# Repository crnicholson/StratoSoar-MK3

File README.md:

# StratoSoar MK3 - UAVs For the Masses

<!-- **TL;DR**: The StratoSoar project is a low-cost, lightweight UAV designed to be dropped from a weather balloon  at any altitude, aiming for autonomous, efficient flight to selected GPS coordinates. The hope is to get a UAV platform in the hands of educators, researchers, and hobbyists alike since StratoSoar is much smaller, lighter, and cheaper than conventional UAVs.  -->

**TL:DR**: The StratoSoar project is a low-cost, lightweight Unmanned Aerial Vehicle (UAV) designed for deployment from a weather balloon at various altitudes, aiming for autonomous and efficient flight to designated GPS coordinates. By offering a more affordable, compact, and lightweight alternative to conventional UAVs, StratoSoar aims to empower educators, researchers, and hobbyists with an accessible platform for exploration and experimentation. 

## Watch The Video

<!-- **WORK IN PROGRESS** - This project is still in the works. I don't recommend using it yet because it has the potential of being dangerous.

**NEW** - Writing code and making the PCB. 

**STATE as of 7/1/24** - Just starting development! -->

<!-- <div style="max-width: 500px; margin: 0 auto;">
  <div style="position: relative; padding-bottom: 56.25%; height: 0; overflow: hidden; max-width: 100%; height: auto;">
    <iframe style="position: absolute; top: 0; left: 0; width: 100%; height: 100%;" src="https://www.youtube.com/embed/TiqkcGWG4g8" title="StratoSoar MK2/3: A Review" frameborder="0" allow="accelerometer; autoplay; clipboard-write; encrypted-media; gyroscope; picture-in-picture; web-share" referrerpolicy="strict-origin-when-cross-origin" allowfullscreen></iframe>
  </div>
</div>

<br /> -->

 | 
-- | --
<i>StratoSoar glider.</i> | <i>StratoSoar MK3.0 circuit board.</i>
 | 
<i>Computational fluid dynamic sims.</i> | <i>Soldering of the board.</i>

## What Is the StratoSoar Project?

StratoSoar is a low-power, adaptive UAV that is dropped from a weather balloon at approximately 5,000 feet, with plans to reach even higher altitudes soon. The main goal of StratoSoar is to fly to selected GPS coordinates efficiently or choose a closer, more realistic landing site without human interaction. The current aim for StratoSoar is to operate on a single 600 mAh 15 gram LiPo battery for a 10+ hour flight. 

## Now, What Is a UAV?

UAVs, or Unmanned Aerial Vehicles, are autonomous aircraft, usually in the form of planes or drones. They have many applications, such as [delivering medicine, food, and supplies](https://www.flyzipline.com/) to remote areas, participating in aerial combat with the military, and conducting aerial imaging.

### Common Types of UAVs Include:

- Quadcopter (typical drones)
- Fixed-wing aircraft (like StratoSoar)

## StratoSoar vs. Conventional UAVs

### Traditional UAVs Are Typically:

- Large (5-15 meter wingspan)
- Heavy (2-20 kg)
- Expensive ($10,000-10,000,000 USD)
- Closed source and proprietary

### StratoSoar Aims to Overcome These Limitations With:

- Weight: less than 250 grams
- Wingspan: 80 cm
- Cost: less than $150 USD
- Open source and accessible

## What Are the Uses of StratoSoar?

I'm currently considering two main concepts: an educational kit for students and hobbyists or a platform designed to study the aerodynamics of the stratosphere, a field with limited existing resources. Additionally, I'm exploring other ideas such as reusable radiosondes, systems for remote delivery of medicine and parcels, and advanced atmospheric monitoring solutions.

<!-- ## What Includes the StratoSoar Project? What Are the Different Parts of it?

StratoSoar has many different parts, and they all combine to make this project. 

- **Code** - All of the code directory, and the programs needed to run it. These include the main `.ino`s and the accompanying `.cpp` and `.h` files, along with the test files for the IMU and GPS.
- **PCB** - The circuit board is the basis of this project, it interfaces the code with the glider. StratoSoar includes the circuit board files and the schematics and everything needed to build a PCB.
- **3D Files** - StratoSoar requires some 3D printed parts to function, but these files also serve as an interactive build guide. StratoSoar includes the 3D files needed to print parts for the glider and the 3D files to assemble the glider.
- **Media** - The images and such of StratoSoar. 
- **Cutdown Mechanism** - This is the thing that helps you release the glider from the balloon payload - or whatever you want to drop it from. This includes all of the above things but will be in a separate GitHub repository.  -->

## How Does StratoSoar Work at a High Level?

<!-- StratoSoar is attached to a weather balloon via the cutdown mechanism. Once the balloon reaches the desired altitude, the cutdown mechanism drops the glider. The glider then descends, steering its way to specified coordinates. 

StratoSoar takes pride in being highly configurable and hackable, so there are many ways you change how it comes down built into the code. 

StratoSoar uses data from an IMU that goes through a Kalman filter to receive accurate AHRS, or Attitude Heading Reference System. This can tell StratoSoar the pitch, yaw, and roll of the glider. Then, StratoSoar integrates a GPS module to get the GPS coordinates. Both the GPS and the AHRS are used to compute the azimuth to find the turning angle of the glider. The turning angle tells the glider how much it needs to turn to be facing the correct yaw that will get the glider to the target location. Additionally, an algorithm is used to get the distance between the glider location's and the target location. 

With the turning angle computed, a PID mechanism is used to control the servo attached to the rudder of the glider. This PID mechanism learn from it's mistakes and can accurately aim the glider in the correct direction. 

Additionally, the glider beacons it's location at a configurable interval with LoRa for tracking. It also allows for a camera module to be added on to take photos and video. 

The glider will fly to the selected coordinates, and depending on the user configuration, will either spiral down or release a parachute above the coordinates once it has reached them to safely descend. Additionally, if the glider is too low in altitude, prior to the flight the user can enter closer coordinates as backup landing locations.  -->

StratoSoar MK3 is an advanced autonomous glider designed to operate at high altitudes, such as those reached by weather balloons. The glider is attached to a weather balloon via a cutdown mechanism. Once the balloon reaches the desired altitude, the cutdown mechanism releases the glider, initiating its descent. The glider then navigates autonomously to specified coordinates, using a combination of sensors, advanced algorithms, and low-power electronics.

### Core Components and Functionality:

- **Autopilot System**:
    - **GPS and IMU Integration**: StratoSoar uses a custom GPS module and an IMU, both designed for low-power operation. The IMU data is processed through a Kalman filter to provide accurate Attitude Heading Reference System (AHRS) data, including pitch, yaw, and roll. This information, combined with GPS coordinates, enables precise navigation.
    - **Advanced Waypoint Navigation**: The waypoint navigation system is designed for complex flight paths, incorporating advanced turning algorithms to ensure smooth and accurate direction changes.
    - **Servo Control with PID**: A PID control mechanism governs the rudder’s servo, ensuring precise adjustments to the glider's course based on real-time feedback.

- **Communication and Data Logging**:
    - **LoRa Telemetry**: The glider continuously beacons its location via LoRa communication, which includes forward error correction for reliable data transmission. This allows for real-time tracking and data collection.
    - **Data Logging**: Critical flight data, including sensor readings and GPS coordinates, are logged using a combination of SD card and EEPROM storage, optimized for low power consumption.
    - **Camera**: If configured, the glider uses a custom designed camera module to take photos at specific coordinates or record the entire flight.  

- **Modularity and Customization**:
    - **Hackability**: StratoSoar is designed to be highly configurable and hackable. Users can customize its descent strategy, whether by spiral descent, parachute deployment, or alternative landing locations. The codebase is modular, allowing for easy modifications or the addition of new features.
    - **Camera Module**: An optional low-power camera module can be added to capture photos or video during the flight, with Python scripts available for post-processing the footage.

- **Ground Station and Data Handling**:
    - **Ground Station**: The ground station, built on an ESP32 platform, receives telemetry data from the glider via LoRa. It logs this data locally and communicates with a server using HTTP requests. A Flask-based uploader script then transfers the data to SondeHub for analysis and storage.

- **PCB Design**:
    - **StratoSoar MK3 PCB**: The main PCB, optimized for power efficiency, size, and cost, integrates over 100 components, managing the various systems onboard.
    - **Additional PCBs**: Supporting PCBs, such as those for the GPS module, LoRa communication, camera, and IMU, are designed for specific tasks, enhancing the glider's overall functionality.

### Operation and Recovery:

Upon release from the weather balloon, StratoSoar begins its guided descent following waypoints or single target coordinate. It calculates the optimal flight path using its GPS and AHRS data, making real-time adjustments to its trajectory through the PID-controlled servo system. Depending on user configurations, the glider can either glide smoothly to the target coordinates, initiate a spiral descent, or deploy a parachute for a safe landing.

If the glider's altitude drops below a certain threshold, backup landing coordinates can be used to ensure a safe recovery. Throughout the flight, the glider’s location is continuously transmitted, allowing for easy tracking and recovery.

## File System and More Project Info

I'm only listing the key items, leaving out all the unnecessary stuff. This should give you a general sense of the project and all its features. Note that this is also only stuff I did during Hack Club Arcade.

- `Code/autopilot`: (5000 lines of code!)
    - `autopilot.ino`: The script that ties all of these files together.
    - `gps.cpp`: GPS code custom-made for low-power.
    - `waypoint.cpp`: Custom waypoint flight with advanced turning.
    - `lora.cpp`: LoRa communications with complex forward error correction.
    - `sd.cpp` + `eeprom.cpp`: Data logging in a low-power manner.
    - `servo.cpp`: Ultra low-power servo functions.
    - `bme280.cpp`: Weather data sensor.
    - `imu.cpp`: An interial measurement unit running a Kalman filter.
- `Code/groundStation`: 
    - `groundStation.ino`: The code for the receiving station of the LoRa telemetry, uses ESP32 and HTTP requests to communicate with the server, also locally logs data. 
    - `uploader/flaskUploader.py`: A Flask server that uses an API to put all the data on SondeHub. 
- `Code/camera`: Utilization of a low-power camera module and Python scripts for conversion.
- `Code/calculator`: Python script to parametrically create flying wing glider. 
- `PCB/StratoSoar-MK3.0`: The main PCB consisting of over 100 components, optimized for power, size, and cost.
- `PCB/gpsBreakout`: A PCB designed for testing a cheap, $2 Chinese GPS module.
- `PCB/loRa`: The ground station to receive the glider's data. 
- `PCB/camera`: A breakout board for a low-power camera module. 
- `PCB/imuBreakout`: One of the first breakout boards made for a new Interial Measurement Unit. 
- `3D Files/cardboardGlider`: Parametric Fusion 360 design for a folding origami glider. 
- `3D Files/StratoSoar Rev2 v36`: High efficiency glider.

## A Quick Note on MK1, MK2, Naming, and Revisions

StratoSoar MK1 was the precursor and the spark to StratoSoar MK2. StratoSoar MK1 was officially developed from October 1st to July 30th, although StratoSoar MK2 was unofficially being worked on in the months of March through June. StratoSoar MK1 failed to fly autonomously, and it also failed to release from the balloon. Major upgrades have been made since then.

StratoSoar MK2 officially started on October 1st, and will end has now ended. It was a success. 

StratoSoar MK3 officially started on June 1st, and will end in quite some time when I launch it from a weather balloon. A new major revision (eg. MK4) will come out every time when I release the glider from the balloon in the Summer. After the Summer, work on the next revision begins, with many updates and new features. 

<!-- A new sub-revision (for lack of better word) comes out every time I make a new PCB. For example, my first version of my PCB was MK2.0. At the time of writing, the current version of StratoSoar is MK2.1. A new version of 3D model is denoted by the Rev number. Rev starts at 0. 0 and 1 are not shown in this repo because they didn't turn out very good. The physical gliders are denoted by the 3D model number. Sometimes a small change is made with glider so the name of the glider is Rev x.x, for example. Sometimes the same happens with the 3D model, again it would be x.x. To put this in practice, the final glider may be MK2.5 Rev 7.3.1. The code has no version history in the way the 3D models and the PCB do. -->

Also, I use "we" a lot in this writing. This usually refers to myself or this project, but it also refers to my small team over at New England Weather Balloon Society.

One last thing. When I refer to StratoSoar, I am referring to the project as a whole, but more specifically, the most recent version. 

<!-- ## Watch my Talk About StratoSoar MK2 The North East HamXpo! -->

## Is This Legal?
Yes! During flight, the ground operator has no ***direct*** control over the flight path, i.e. via a radio. Because of this, and it being unpowered, it qualifies as a free flight glider. Free flight gliders have very little regulations. You can think of them as a paper airplane. 

## Can I Buy a Kit or a Complete Product?

Currently, StratoSoar is not available to purchase online as a kit or complete product. We have plans in the next few years to release a kit for schools, education centers, hobbyists and a complete product for industry at an affordable price. You are welcome to make one in the mean time!

## How Can I Make One? Are There Docs?

One of the goals of StratoSoar was to make an affordable and open source system for anyone to perform stratospheric research, so all the files are available for free. This means that you can construct StratoSoar from scratch. **A guide to do this will be available soon.**

<!-- It is still in the works, but you can check out `DOCS.md` under the `Docs` folder.**  -->

## Helpful Sources and Credits

I'm in the midst of compiling this.

## Cutdown Mechanism

[See my other WIP GitHub repo.](https://github.com/crnicholson/Cutdown-Mechanism)

## Funding and Support

We currently have <u>**very**</u> limited funding to complete this project. We would **love any donations or sponsorships** we could get to elevate (no pun intended) this project to the next level. If you don't want to donate, but want to help out, we would love your support with other areas of this project. Reach out to me if you have interest at:

- [newbsballoons@gmail.com](mailto:newbsballoons@gmail.com) (organization email, recommended).

- [charlienicholsonr@gmail.com](mailto:charlienicholsonr@gmail.com) (personal email).

## Special Thanks

This project would not be possible without the following individuals:

- Max Kendall (W0MXX) for working closely together with me.

- Mike Malis for helping with the design of the glider. 

- Brett Miwa for schematic review, PCB design, electrical theory, and boost converter circuitry design.

- Bob Phinney (K5TEC) for providing NEST and securing funding.

- Mark Jessop (VK5QI) for answering all of my questions.

- Mike Hojnowski (KD2EAT) for PCB design and hardware/software debugging.

- Paul Hamilton for helping me with FAA regulations.

- My parents!

And these entities:

- Hack Club, for providing support for projects like this. 

- New England Sci-Tech (NEST) for providing a maker space to work, funding, and hosting NEWBS.

- New England Weather Balloon Society (NEWBS) for expertise and the opportunity.

- Bagel Fund, for providing funding. 

## Affiliate Programs and Projects

- **Hack Club** - Hack Club is a non-profit designed for teenagers that provides support for projects like this. 
- **NEWBS** - Max and Seth Kendall of NEWBS, or New England Weather Balloon Society, are helping me launch my project from a balloon. They are dedicated to helping people in New England launch weather balloons. 
- **New England Sci-Tech** - Bob Phinney of NEST is hosting NEWBS. NEST is a great maker space. If you are in the Greater Boston Area, go check them out!
- **StratoScience** - This is the official class that I'm in helping me launch my project. This is a high altitude engineering class for teens. Check them out if your are in the Greater Boston area!

## Still Have Questions?

Do you have any questions? Are the docs incomplete and you want to ask anything? Do you just want to say hi (or how cool my project is!)?

Reach out to me at [charlienicholsonr@gmail.com](mailto:charlienicholsonr@gmail.com).

## Flights

# Mid August

The glider was realeased from 5,000 feet. You can see the launch video [here](https://www.youtube.com/watch?v=DZU_8TDUlJg). You can find data on the release [here](https://www.youtube.com/watch?v=TiqkcGWG4g8).

## License

Both the software and documentation are under the [GNU GPL v3 license](https://choosealicense.com/licenses/gpl-3.0/). The hardware and the 3D files are under the [CERN Open Hardware Licence Version 2 - Strongly Reciprocal](https://choosealicense.com/licenses/cern-ohl-s-2.0/). The media is under the [CC BY 4.0 DEED](https://creativecommons.org/licenses/by/4.0/).

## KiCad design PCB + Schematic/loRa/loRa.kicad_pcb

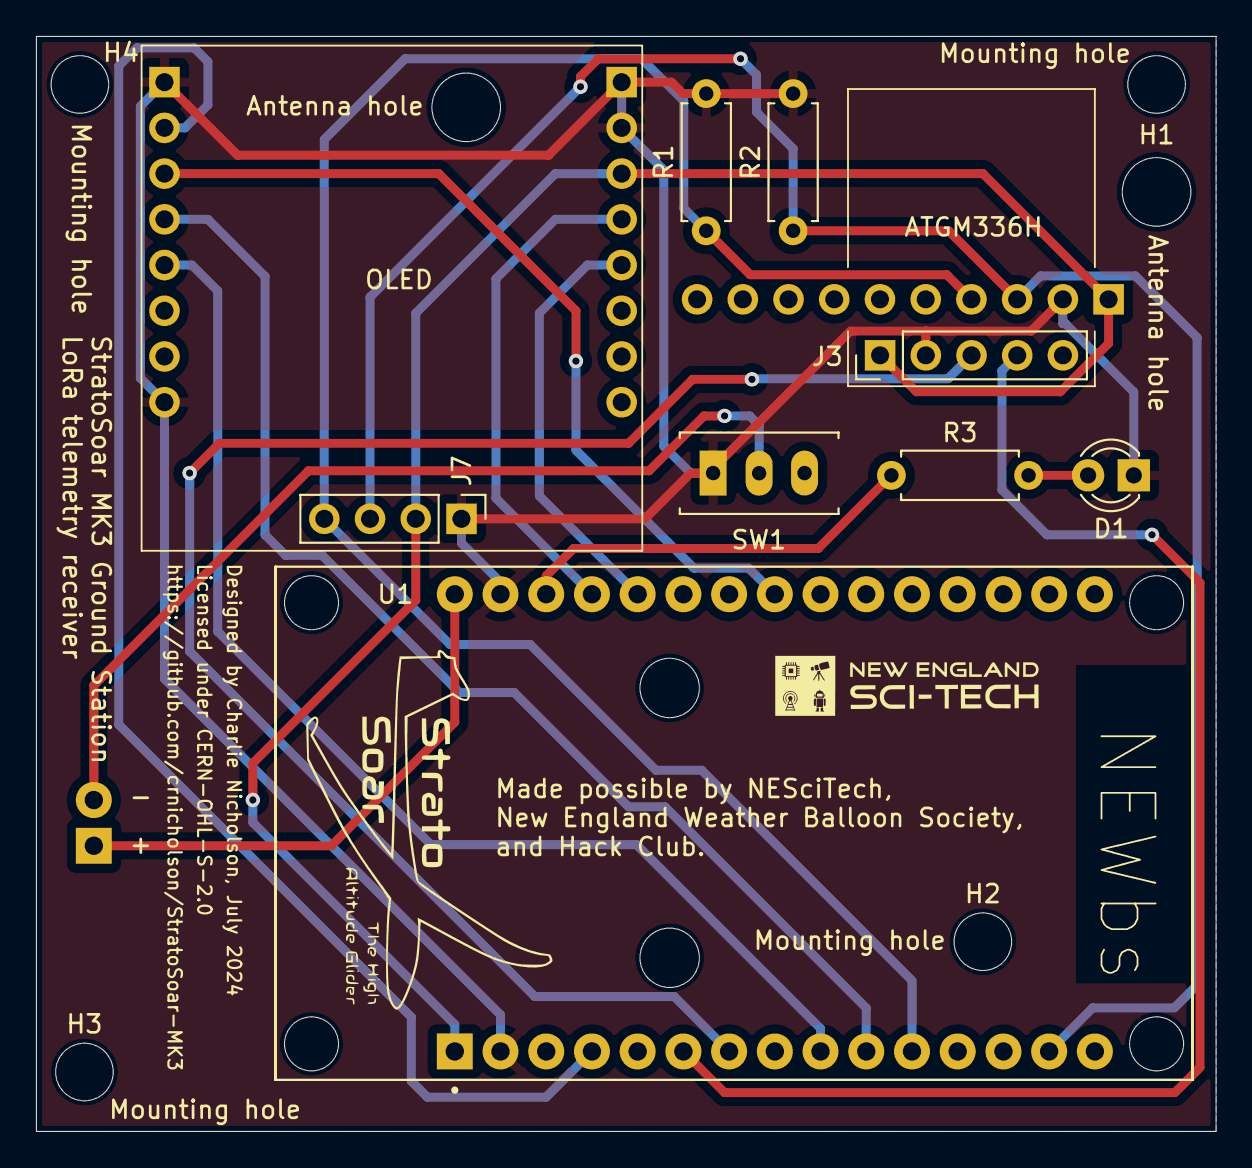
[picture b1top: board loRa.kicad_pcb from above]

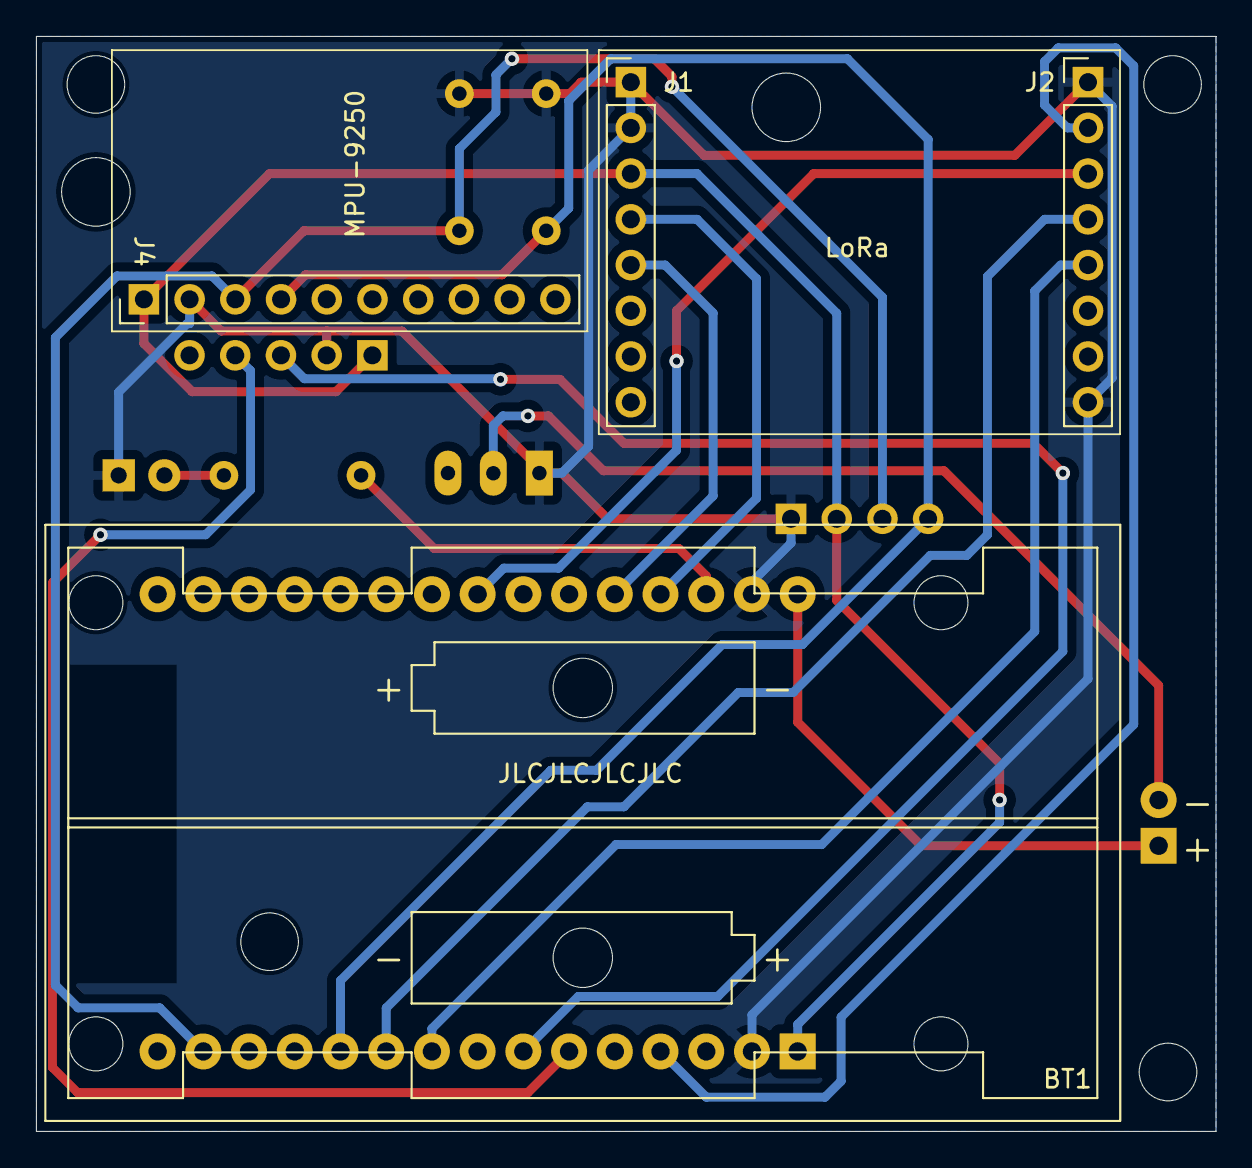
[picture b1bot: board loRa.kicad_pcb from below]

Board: 2 copper layers, 65.5 x 60.8 mm, 16 parts (4 on the bottom side), 16 nets.

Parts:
BT1: 3V; BatteryHolder_Keystone_2462_2xAA
D1: RED; LED_D3.0mm
H1, H2, H3, H4: MountingHole; MountingHole_3.2mm_M3
J1: Left; PinHeader_1x08_P2.54mm_Vertical
J2: Right; PinHeader_1x08_P2.54mm_Vertical
J3: GPS; PinHeader_1x05_P2.54mm_Vertical
J4: MPU-9250; PinHeader_1x10_P2.54mm_Vertical
J7: OLED; PinHeader_1x04_P2.54mm_Vertical
R1, R2: 1.8 K; R_Axial_DIN0207_L6.3mm_D2.5mm_P7.62mm_Horizontal
R3: 1 K; R_Axial_DIN0207_L6.3mm_D2.5mm_P7.62mm_Horizontal
SW1: SW_SPDT; SW_Slide_SPDT
U1: ESP32-DEVKIT-V1; MODULE_ESP32_DEVKIT_V1

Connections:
+3.3V: J1.3, J3.1, J4.1, J7.2, U1.1 (3V3)
+BATT: BT1.1 (+), U1.30 (VIN)
CS: J2.2, U1.4 (D2)
DIO0: J1.5, U1.26 (D14)
GND: D1.1 (K), J1.1, J1.2, J2.1, J2.8, J3.2, J4.2, J7.1, R1.2, R2.2, SW1.1 (A), U1.2 (GND), U1.29 (GND)
LED: R3.1, U1.28 (D13)
LORA_RST: J1.4, U1.27 (D12)
MISO: J2.4, U1.10 (D19)
MOSI: J2.3, U1.23 (D25)
unnamed: BT1.2 (-), SW1.2 (B)
unnamed: D1.2 (A), R3.2
RX: J3.4, U1.6 (RX2)
SCK: J2.5, U1.9 (D18)
SCL: J4.3, J7.3, R2.1, U1.14 (D22)
SDA: J4.4, J7.4, R1.1, U1.11 (D21)
TX: J3.3, U1.7 (TX2)

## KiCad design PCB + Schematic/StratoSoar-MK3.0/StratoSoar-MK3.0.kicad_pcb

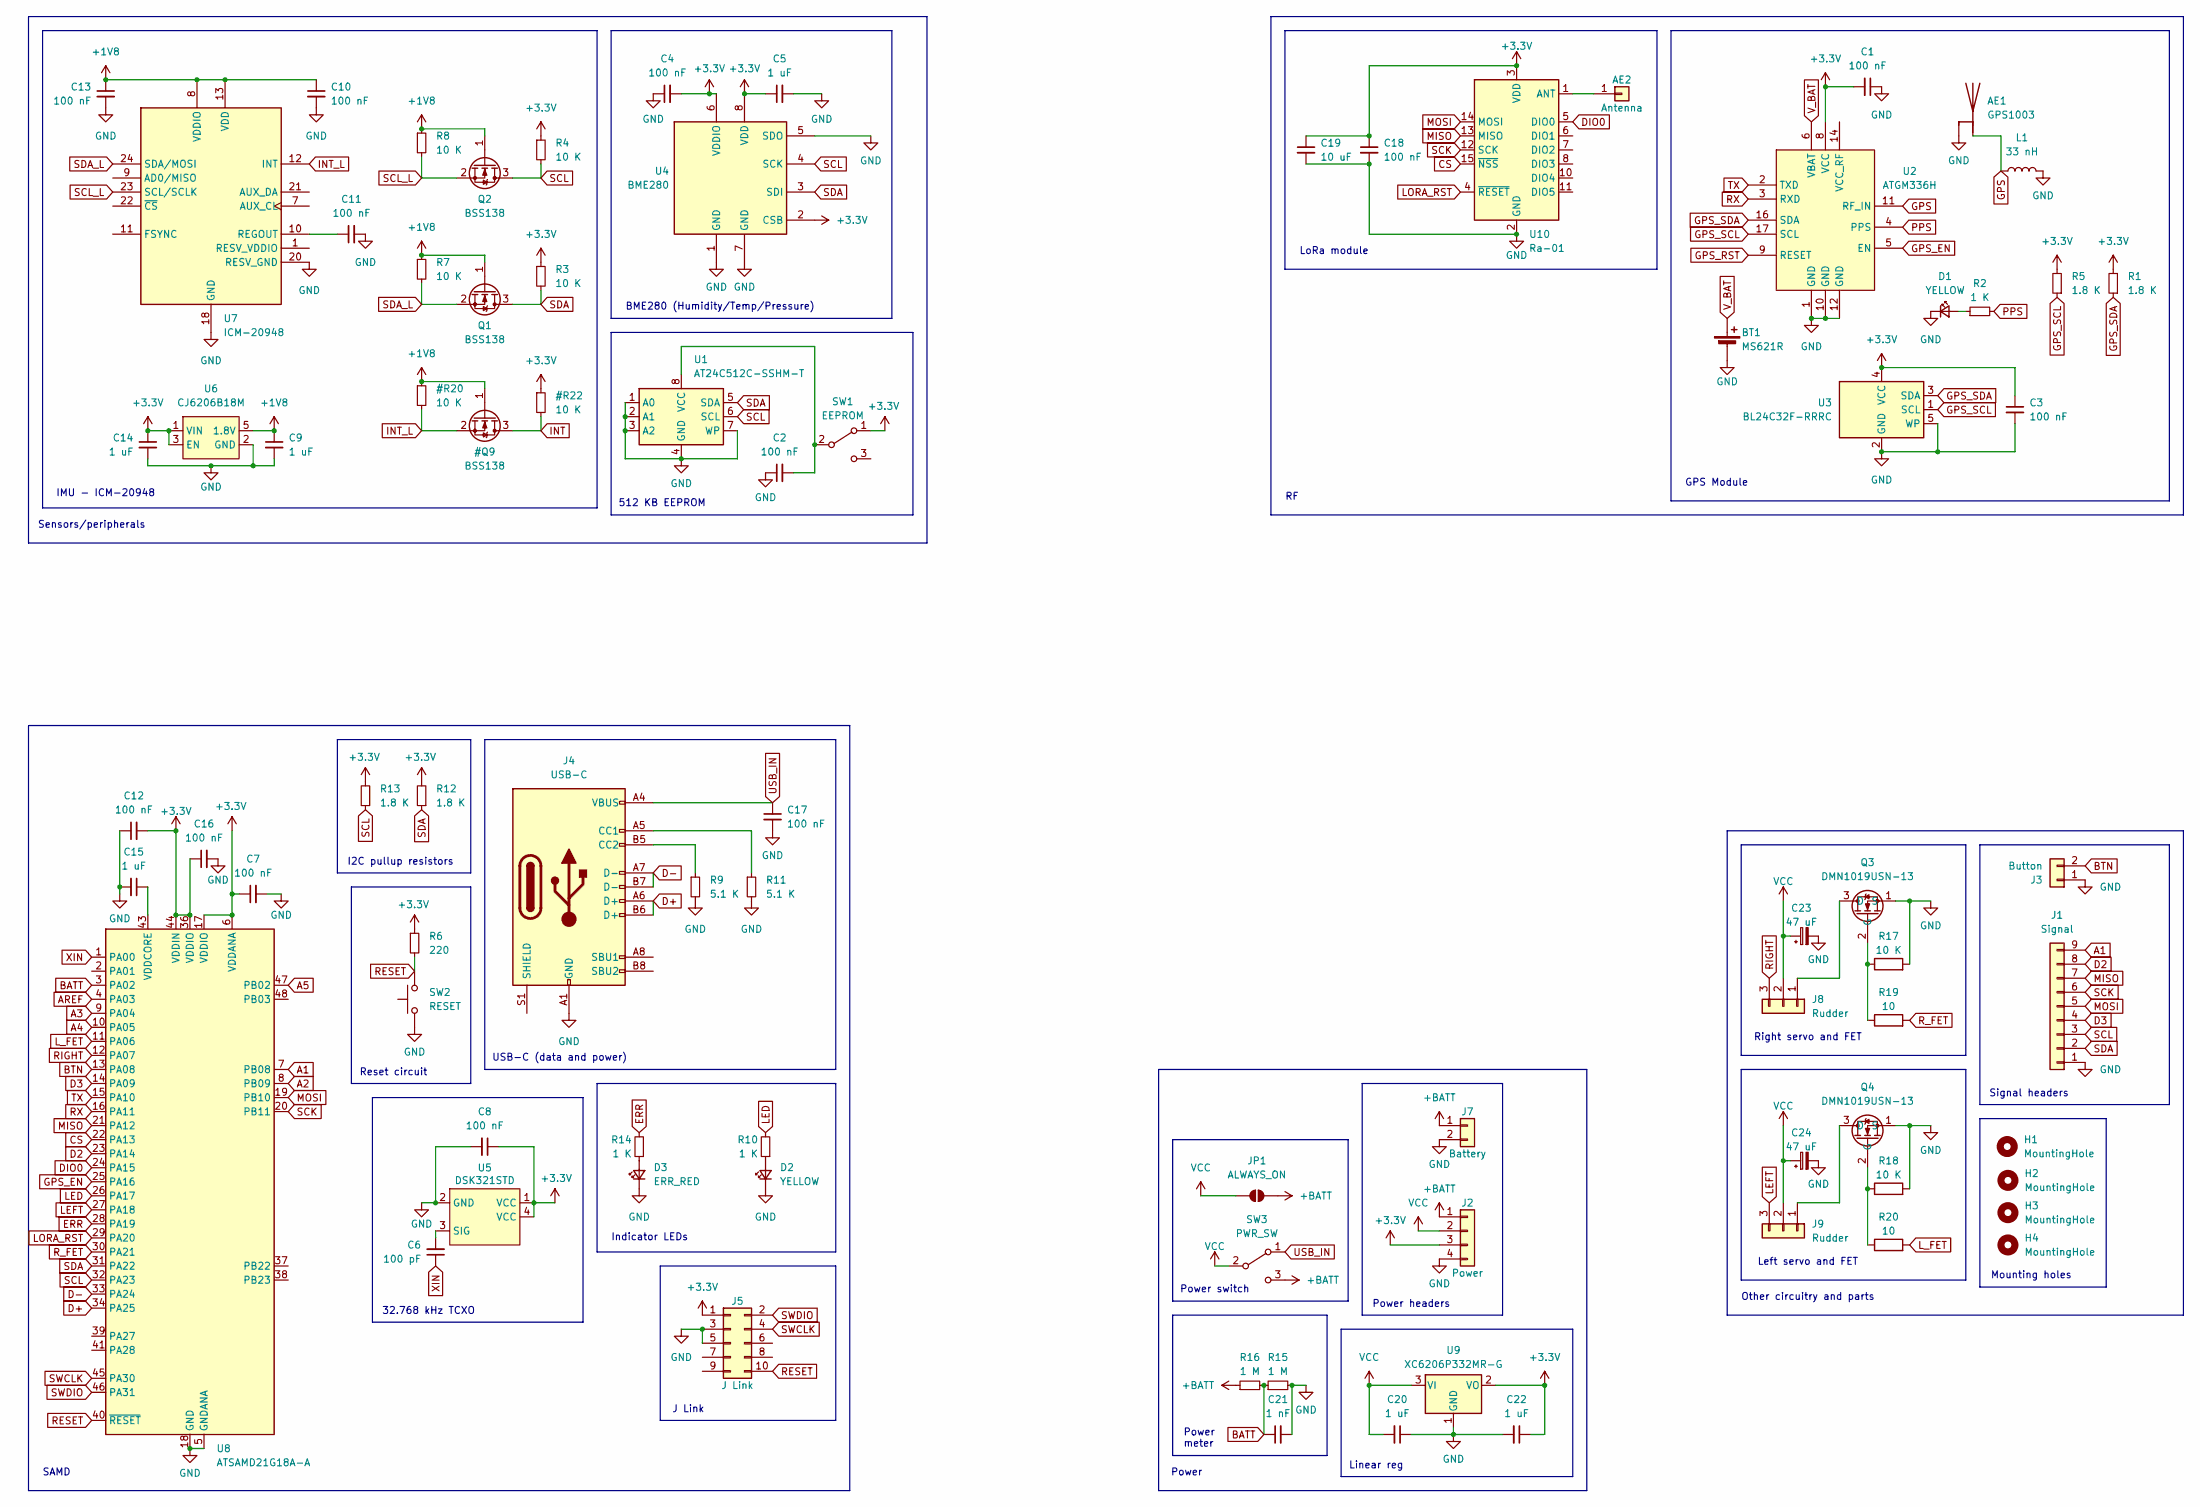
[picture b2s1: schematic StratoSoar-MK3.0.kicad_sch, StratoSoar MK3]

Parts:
AE1: GPS1003
AE2: Antenna; PinHeader_1x01_P2.54mm_Vertical
BT1: MS621R
C1, C17, C18: 100 nF; C_0603_1608Metric; LCSC C14663
C2, C3, C4, C7, C8, C10, C11, C12, C13, C16: 100 nF; C_0402_1005Metric; LCSC C1525
C5, C15: 1 uF; C_0402_1005Metric; LCSC C52923
C6: 100 pF; C_0402_1005Metric; LCSC C1546
C9, C14, C20, C22: 1 uF; C_0603_1608Metric; LCSC C15849
C19: 10 uF; C_0603_1608Metric; LCSC C19702
C21: 1 nF; C_0402_1005Metric; LCSC C1523
C23, C24: 47 uF; C_1206_3216Metric; LCSC C139825
D1, D2: YELLOW; LED_0603_1608Metric; LCSC C72038
D3: ERR_RED; LED_0603_1608Metric; LCSC C2286
H1, H2, H3, H4: MountingHole; MountingHole_2.2mm_M2
J1: Signal; PinHeader_1x09_P2.54mm_Vertical
J2: Power; PinHeader_1x04_P2.54mm_Vertical
J3: Button; PinHeader_1x02_P2.54mm_Vertical
J4: USB-C; USB_C_Receptacle_GCT_USB4105-xx-A_16P_TopMnt_Horizontal; LCSC C136423
J5: J Link; PinHeader_2x05_P1.27mm_Vertical_SMD; LCSC C2881910
J7: Battery; PinHeader_1x02_P2.54mm_Vertical
J8, J9: Rudder; PinHeader_1x03_P2.54mm_Vertical
JP1: ALWAYS_ON; SolderJumper-2_P1.3mm_Open_RoundedPad1.0x1.5mm
L1: 33 nH; L_0402_1005Metric; LCSC C90178
Q1, Q2: BSS138; SOT-23; LCSC C5224268
Q3, Q4: DMN1019USN-13; SC-59_Handsoldering; LCSC C145103
R1, R5, R12, R13: 1.8 K; R_0603_1608Metric; LCSC C4177
R2, R10, R14: 1 K; R_0402_1005Metric; LCSC C11702
R3, R4, R7, R8, R17, R18: 10 K; R_0402_1005Metric; LCSC C25744
R6: 220; R_0402_1005Metric; LCSC C25091
R9, R11: 5.1 K; R_0402_1005Metric; LCSC C25905
R15, R16: 1 M; R_0402_1005Metric; LCSC C26083
R19, R20: 10; R_0402_1005Metric; LCSC C25077
SW1: EEPROM; SW_SPDT_PCM12; LCSC C963206
SW2: RESET; SW_SPST_CK_RS282G05A3; LCSC C2888954
SW3: PWR_SW; SW_SPDT_PCM12; LCSC C963206
U1: AT24C512C-SSHM-T; SOIC-8_3.9x4.9mm_P1.27mm; LCSC C54668
U2: ATGM336H; LCSC C90770
U3: BL24C32F-RRRC; SOT-23-5; LCSC C5185883
U4: BME280; Bosch_LGA-8_2.5x2.5mm_P0.65mm_ClockwisePinNumbering; LCSC C92489
U5: DSK321STD; Oscillator_SMD_EuroQuartz_XO32-4Pin_3.2x2.5mm; LCSC C383430
U6: CJ6206B18M; SOT-23-5; LCSC C2829375
U7: ICM-20948; InvenSense_QFN-24_3x3mm_P0.4mm; LCSC C726001
U8: ATSAMD21G18A-A; TQFP-48_7x7mm_P0.5mm; LCSC C78624
U9: XC6206P332MR-G; SOT-23-3; LCSC C5446
U10: Ra-01; Ai-Thinker-Ra-01-LoRa; LCSC C2830750

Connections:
+BATT: J2.1, J7.1, JP1.2 (B), R16.1, SW3.3 (C)
A1: J1.9, U8.7 (PB08)
A2: U8.8 (PB09)
A3: U8.9 (PA04)
A4: U8.10 (PA05)
A5: U8.47 (PB02)
AREF: U8.4 (PA03)
BATT: C21.1, R15.1, R16.2, U8.3 (PA02)
BTN: J3.2, U8.13 (PA08)
CS: U8.22 (PA13), U10.15 (~NSS)
D2: J1.8, U8.23 (PA14)
D3: J1.4, U8.14 (PA09)
D+: J4.A6 (D+), J4.B6 (D+), U8.34 (PA25)
D-: J4.A7 (D-), J4.B7 (D-), U8.33 (PA24)
DIO0: U8.24 (PA15), U10.5 (DIO0)
ERR: R14.2, U8.28 (PA19)
GND: AE1.2 (GND), BT1.2 (-), C1.1, C2.1, C3.2, C4.1, C5.2, C7.2, C8.2, C9.2, C10.2, C11.2, C12.1, C13.2, C14.2, C15.2, C16.2, C17.2, C18.2, C19.2, C20.1, C21.2, C22.2, C23.2, C24.2, D1.1 (K), D2.1 (K), D3.1 (K), J1.1, J2.4, J3.1, J4.A1 (GND), J4.A12 (GND), J4.B1 (GND), J4.B12 (GND), J5.3, J5.5, J7.2, L1.2, Q3.1 (S), Q4.1 (S), R9.2, R11.2, R15.2, R17.2, R18.2, SW2.1, U1.1 (A0), U1.2 (A1), U1.3 (A2), U1.4 (GND), U1.7 (WP), U2.1 (GND), U2.10 (GND), U2.12 (GND), U3.2 (GND), U3.5 (WP), U4.1 (GND), U4.5 (SDO), U4.7 (GND), U5.2 (GND), U6.2 (GND), U7.18 (GND), U7.20 (RESV_GND), U8.5 (GNDANA), U8.18 (GND), U8.35 (GND), U8.42 (GND), U9.1 (GND), U10.2 (GND), U10.9 (GND), U10.16 (GND)
GPS: AE1.1 (FEED), L1.1, U2.11 (RF_IN)
GPS_EN: U2.5 (EN), U8.25 (PA16)
GPS_RST: U2.9 (RESET)
GPS_SCL: R5.1, U2.17 (SCL), U3.1 (SCL)
GPS_SDA: R1.1, U2.16 (SDA), U3.3 (SDA)
LED: R10.2, U8.26 (PA17)
LEFT: J9.3, U8.27 (PA18)
LORA_RST: U8.29 (PA20), U10.4 (~RESET)
L_FET: R20.2, U8.11 (PA06)
MISO: J1.7, U8.21 (PA12), U10.13 (MISO)
MOSI: J1.5, U8.19 (PB10), U10.14 (MOSI)
unnamed: AE2.1, U10.1 (ANT)
unnamed: D1.2 (A), R2.1
unnamed: D2.2 (A), R10.1
unnamed: D3.2 (A), R14.1
unnamed: J4.A5 (CC1), R11.1
unnamed: J4.B5 (CC2), R9.1
unnamed: J8.1, Q3.3 (D)
unnamed: J9.1, Q4.3 (D)
unnamed: Q3.2 (G), R17.1, R19.1
unnamed: Q4.2 (G), R18.1, R20.1
unnamed: C2.2, SW1.2 (B), U1.8 (VCC)
unnamed: C6.2, U5.3 (SIG)
unnamed: C11.1, U7.10 (REGOUT)
unnamed: C15.1, U8.43 (VDDCORE)
PPS: R2.2, U2.4 (PPS)
RESET: J5.10, R6.2, SW2.2, U8.40 (~RESET)
RIGHT: J8.3, U8.12 (PA07)
RX: U2.3 (RXD), U8.16 (PA11)
R_FET: R19.2, U8.30 (PA21)
SCK: J1.6, U8.20 (PB11), U10.12 (SCK)
SCL: J1.3, Q2.3 (D), R4.2, R13.1, U1.6 (SCL), U4.4 (SCK), U8.32 (PA23)
SCL_L: Q2.2 (S), R8.2, U7.23 (SCL/SCLK)
SDA: J1.2, Q1.3 (D), R3.2, R12.1, U1.5 (SDA), U4.3 (SDI), U8.31 (PA22)
SDA_L: Q1.2 (S), R7.2, U7.24 (SDA/MOSI)
SWCLK: J5.4, U8.45 (PA30)
SWDIO: J5.2, U8.46 (PA31)
TX: U2.2 (TXD), U8.15 (PA10)
USB_IN: C17.1, J4.A4 (VBUS), J4.A9 (VBUS), J4.B4 (VBUS), J4.B9 (VBUS), SW3.1 (A)
VCC: C20.2, C23.1, C24.1, J2.2, J8.2, J9.2, JP1.1 (A), SW3.2 (B), U9.3 (VI)
V_BAT: BT1.1 (+), U2.6 (VBAT)
XIN: C6.1, U8.1 (PA00)

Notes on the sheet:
Power switch
32.768 kHz TCXO
Reset circuit
512 KB EEPROM
Other circuitry and parts
Signal headers
Right servo and FET
GPS Module
J Link
Sensors/peripherals
LoRa module
Left servo and FET
USB-C (data and power)
Power
Indicator LEDs
BME280 (Humidity/Temp/Pressure)
IMU - ICM-20948
I2C pullup resistors
Linear reg
Mounting holes
Power headers
Power meter
SAMD

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
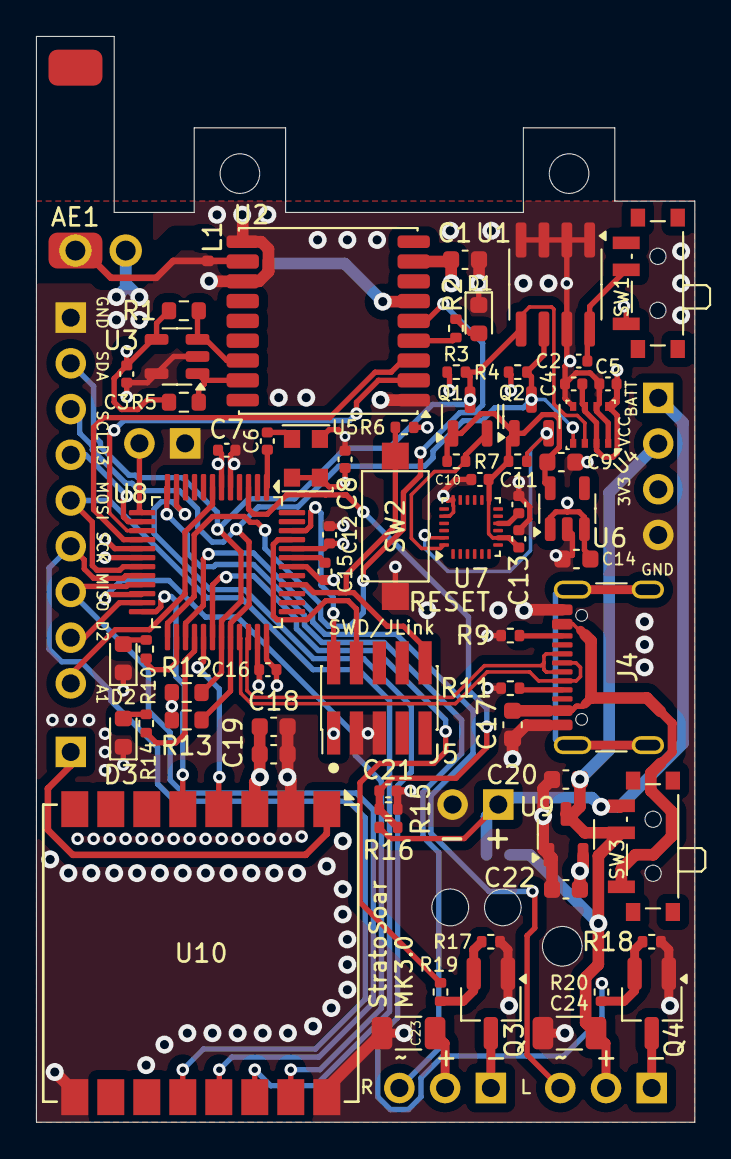
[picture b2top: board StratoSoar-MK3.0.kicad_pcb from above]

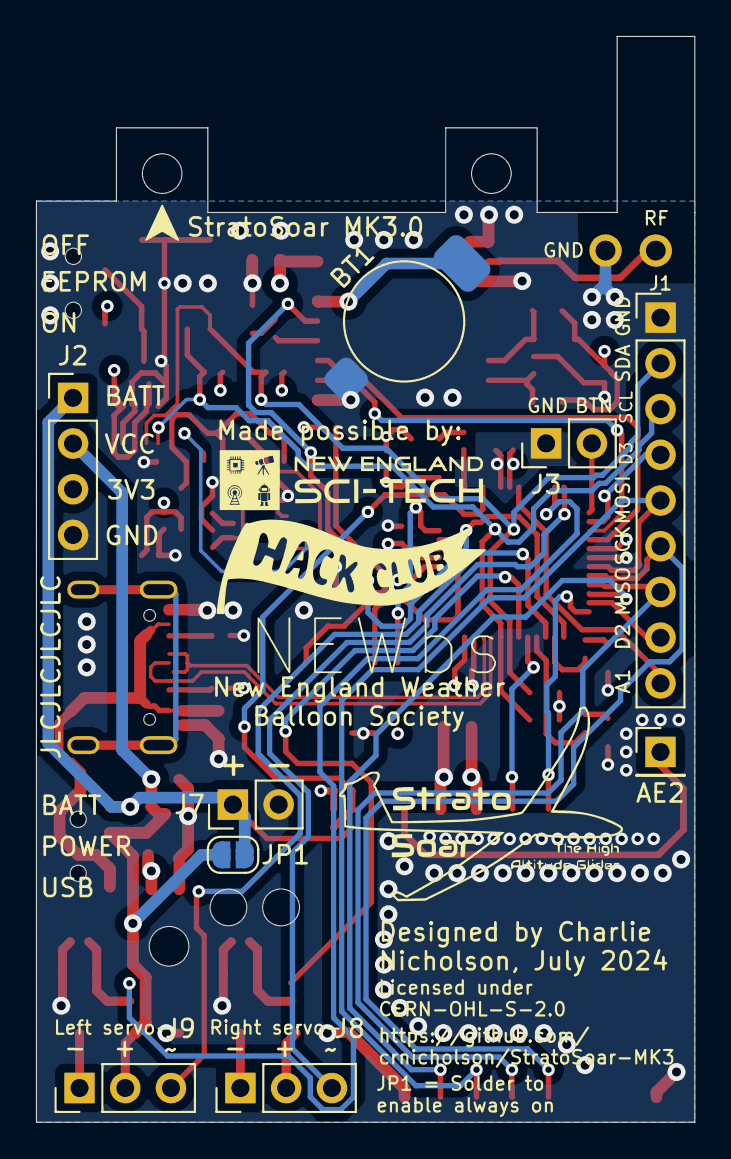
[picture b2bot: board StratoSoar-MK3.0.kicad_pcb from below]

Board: 4 copper layers, 36.6 x 60.3 mm, 81 parts (9 on the bottom side), 55 nets.

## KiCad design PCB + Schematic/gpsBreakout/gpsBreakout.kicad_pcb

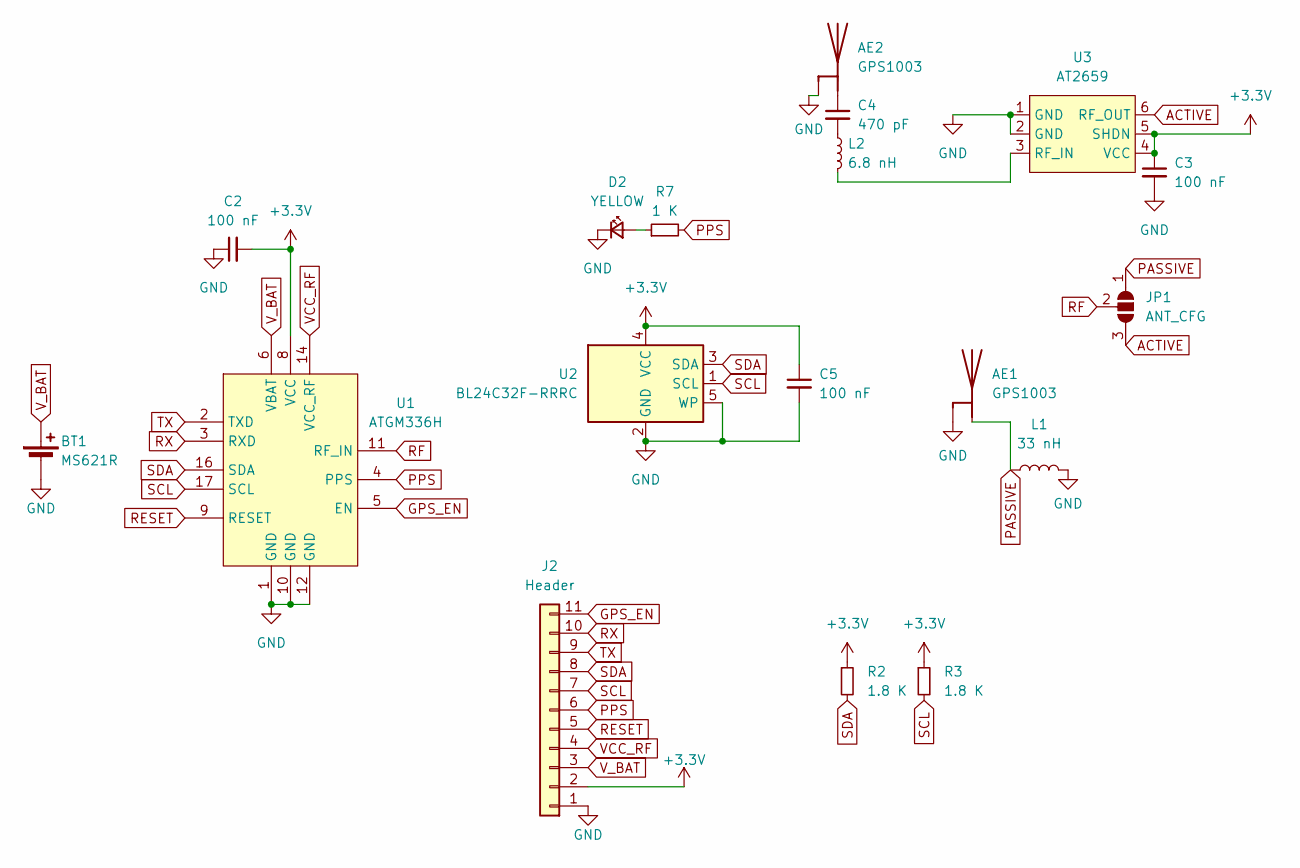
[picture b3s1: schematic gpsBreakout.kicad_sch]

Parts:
AE1, AE2: GPS1003
BT1: MS621R
C2, C3, C5: 100 nF; C_0603_1608Metric; LCSC C14663
C4: 470 pF; C_0402_1005Metric; LCSC C1567
D2: YELLOW; LED_0603_1608Metric; LCSC C72038
J2: Header; PinHeader_1x11_P2.54mm_Vertical
JP1: ANT_CFG; SolderJumper-3_P1.3mm_Open_RoundedPad1.0x1.5mm
L1: 33 nH; L_0402_1005Metric; LCSC C90178
L2: 6.8 nH; L_0402_1005Metric; LCSC C84403
R2, R3: 1.8 K; R_0603_1608Metric; LCSC C4177
R7: 1 K; R_0402_1005Metric; LCSC C11702
U1: ATGM336H; LCSC C90770
U2: BL24C32F-RRRC; SOT-23-5; LCSC C5185883
U3: AT2659; DFN150X100X80-6N; LCSC C92450

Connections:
+3.3V: C2.2, C3.1, C5.1, J2.2, R2.1, R3.1, U1.8 (VCC), U2.4 (VCC), U3.4 (VCC), U3.5 (SHDN)
ACTIVE: JP1.3 (B), U3.6 (RF_OUT)
GND: AE1.2 (GND), AE2.2 (GND), BT1.2 (-), C2.1, C3.2, C5.2, D2.1 (K), J2.1, L1.2, U1.1 (GND), U1.10 (GND), U1.12 (GND), U2.2 (GND), U2.5 (WP), U3.1 (GND), U3.2 (GND)
GPS_EN: J2.11, U1.5 (EN)
unnamed: AE2.1 (FEED), C4.1
unnamed: C4.2, L2.1
unnamed: D2.2 (A), R7.1
unnamed: L2.2, U3.3 (RF_IN)
PASSIVE: AE1.1 (FEED), JP1.1 (A), L1.1
PPS: J2.6, R7.2, U1.4 (PPS)
RESET: J2.5, U1.9 (RESET)
RF: JP1.2 (C), U1.11 (RF_IN)
RX: J2.10, U1.3 (RXD)
SCL: J2.7, R3.2, U1.17 (SCL), U2.1 (SCL)
SDA: J2.8, R2.2, U1.16 (SDA), U2.3 (SDA)
TX: J2.9, U1.2 (TXD)
VCC_RF: J2.4, U1.14 (VCC_RF)
V_BAT: BT1.1 (+), J2.3, U1.6 (VBAT)

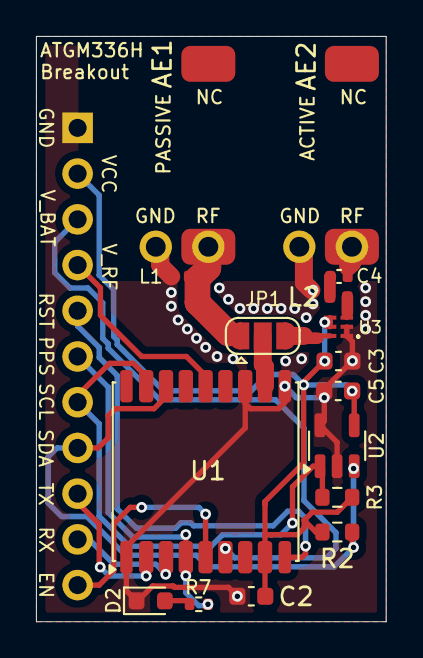
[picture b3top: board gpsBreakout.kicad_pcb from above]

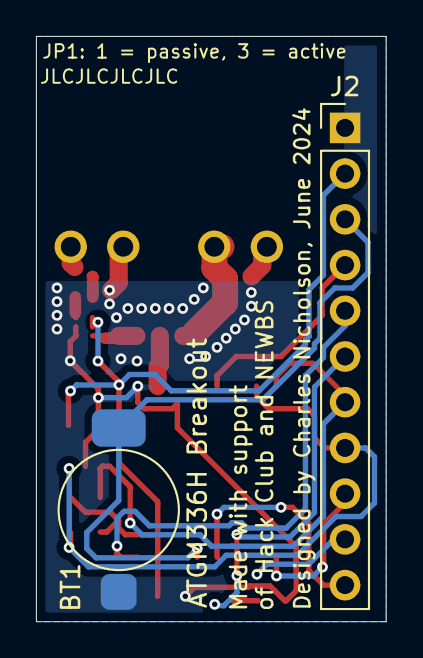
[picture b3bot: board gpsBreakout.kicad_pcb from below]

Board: 2 copper layers, 19.4 x 32.5 mm, 18 parts (2 on the bottom side), 18 nets.

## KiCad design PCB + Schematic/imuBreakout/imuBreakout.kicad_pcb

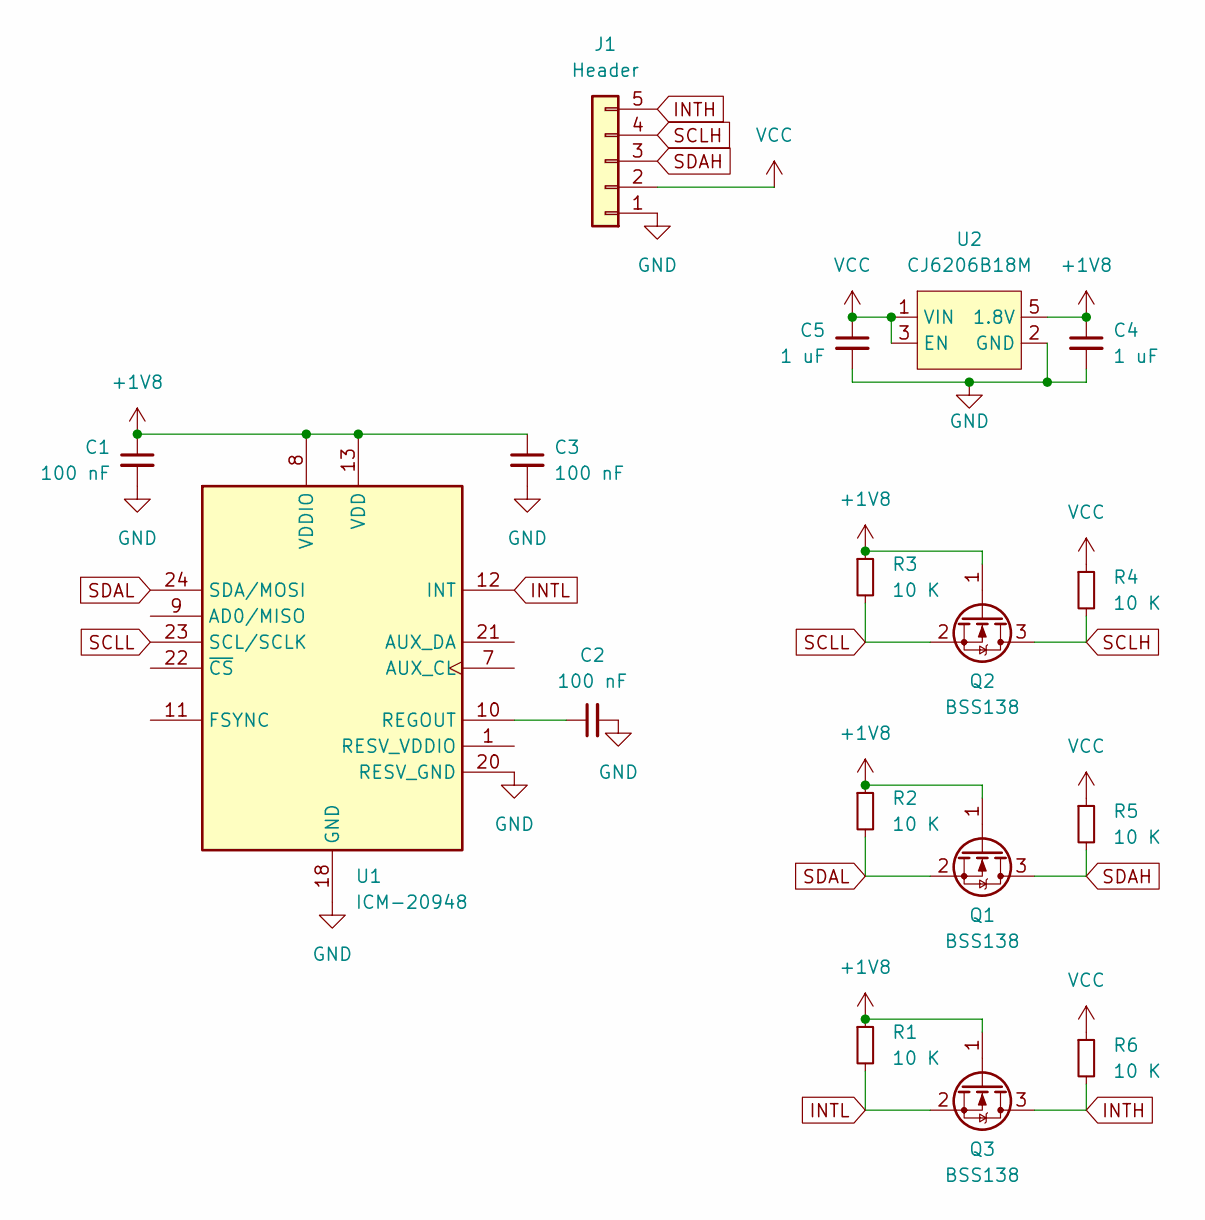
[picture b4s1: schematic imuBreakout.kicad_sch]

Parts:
C1, C2, C3: 100 nF; C_0402_1005Metric; LCSC C1525
C4, C5: 1 uF; C_0402_1005Metric; LCSC C52923
J1: Header; PinHeader_1x05_P2.54mm_Vertical
Q1, Q2, Q3: BSS138; SOT-23; LCSC C5224268
R1, R2, R3, R4, R5, R6: 10 K; R_0402_1005Metric; LCSC C25744
U1: ICM-20948; InvenSense_QFN-24_3x3mm_P0.4mm; LCSC C726001
U2: CJ6206B18M; SOT-23-5; LCSC C2829375

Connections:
+1V8: C1.1, C3.1, C4.1, Q1.1 (G), Q2.1 (G), Q3.1 (G), R1.1, R2.1, R3.1, U1.8 (VDDIO), U1.13 (VDD), U2.5 (1.8V)
GND: C1.2, C2.2, C3.2, C4.2, C5.2, J1.1, U1.18 (GND), U1.20 (RESV_GND), U2.2 (GND)
INTH: J1.5, Q3.3 (D), R6.2
INTL: Q3.2 (S), R1.2, U1.12 (INT)
unnamed: C2.1, U1.10 (REGOUT)
SCLH: J1.4, Q2.3 (D), R4.2
SCLL: Q2.2 (S), R3.2, U1.23 (SCL/SCLK)
SDAH: J1.3, Q1.3 (D), R5.2
SDAL: Q1.2 (S), R2.2, U1.24 (SDA/MOSI)
VCC: C5.1, J1.2, R4.1, R5.1, R6.1, U2.1 (VIN), U2.3 (EN)

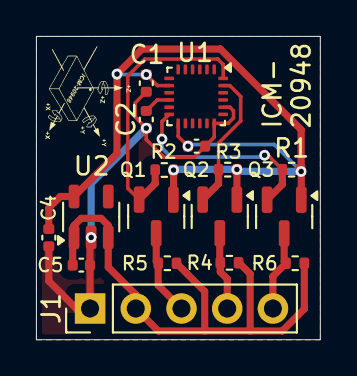
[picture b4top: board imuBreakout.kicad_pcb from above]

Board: 2 copper layers, 15.8 x 16.8 mm, 17 parts (0 on the bottom side), 10 nets.

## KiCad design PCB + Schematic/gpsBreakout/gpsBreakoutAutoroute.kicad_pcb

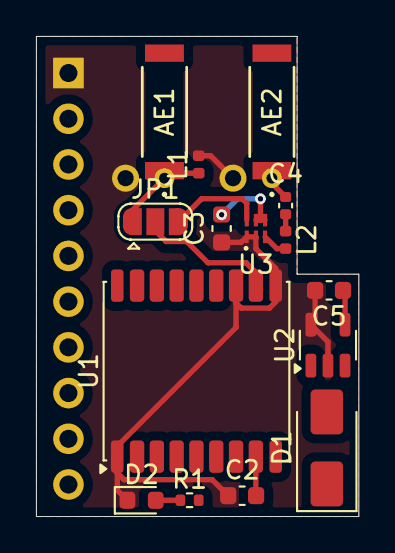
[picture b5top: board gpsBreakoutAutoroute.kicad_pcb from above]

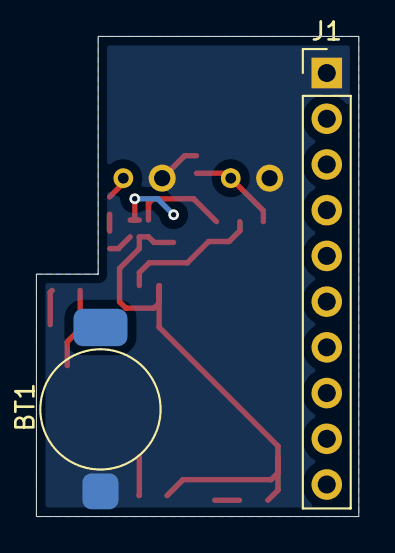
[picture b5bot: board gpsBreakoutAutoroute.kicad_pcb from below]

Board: 2 copper layers, 17.9 x 26.7 mm, 17 parts (2 on the bottom side), 17 nets.

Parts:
AE1, AE2: 1575AT43A0040001E; ANT_1575AT_JOT-L
BT1: MS621R
C2, C3, C5: 100 nF; C_0603_1608Metric
C4: 470 pF; C_0402_1005Metric
D1: SS14; D_SMA
D2: RED; LED_0603_1608Metric
J1: Header; PinHeader_1x10_P2.54mm_Vertical
JP1: ANT_CFG; SolderJumper-3_P1.3mm_Open_RoundedPad1.0x1.5mm
L1: 33 nH; L_0402_1005Metric
L2: 6.8 nH; L_0402_1005Metric
R1: 1 K; R_0402_1005Metric
U1: ATGM336H
U2: AT24CS32-STUM; SOT-23-5
U3: AT2659; DFN150X100X80-6N

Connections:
+3.3V: C2.2, C3.1, C5.1, D1.2 (A), J1.2, U1.5 (EN), U1.8 (VCC), U2.4 (VCC), U3.4 (VCC), U3.5 (SHDN)
ACTIVE: JP1.3 (B), U3.6 (RF_OUT)
GND: AE1.2 (GND), AE2.2 (GND), BT1.2 (-), C2.1, C3.2, C5.2, D2.1 (K), J1.1, L1.2, U1.1 (GND), U1.10 (GND), U1.12 (GND), U2.2 (GND), U2.5 (WP), U3.1 (GND), U3.2 (GND)
unnamed: AE2.1 (FEED), C4.1
unnamed: C4.2, L2.1
unnamed: D2.2 (A), R1.1
unnamed: L2.2, U3.3 (RF_IN)
PASSIVE: AE1.1 (FEED), JP1.1 (A), L1.1
PPS: J1.6, R1.2, U1.4 (PPS)
RESET: J1.5, U1.9 (RESET)
RF: JP1.2 (C), U1.11 (RF_IN)
RX: J1.10, U1.3 (RXD)
SCL: J1.7, U1.17 (SCL), U2.1 (SCL)
SDA: J1.8, U1.16 (SDA), U2.3 (SDA)
TX: J1.9, U1.2 (TXD)
VBAT: BT1.1 (+), D1.1 (K), J1.3, U1.6 (VBAT)
VCC_RF: J1.4, U1.14 (VCC_RF)

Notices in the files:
README.md:
License:
Both the software and documentation are under the [GNU GPL v3 license](https://choosealicense.com/licenses/gpl-3.0/). The hardware and the 3D files are under the [CERN Open Hardware Licence Version 2 - Strongly Reciprocal](https://choosealicense.com/licenses/cern-ohl-s-2.0/). The media is under the [CC BY 4.0 DEED](https://creativecommons.org/licenses/by/4.0/).
PCB + Schematic/StratoSoar-MK3.0/StratoSoar-MK3.0.kicad_pcb:
Licensed under
CERN-OHL-S-2.0
PCB + Schematic/loRa/loRa.kicad_pcb:
Licensed under CERN-OHL-S-2.0
